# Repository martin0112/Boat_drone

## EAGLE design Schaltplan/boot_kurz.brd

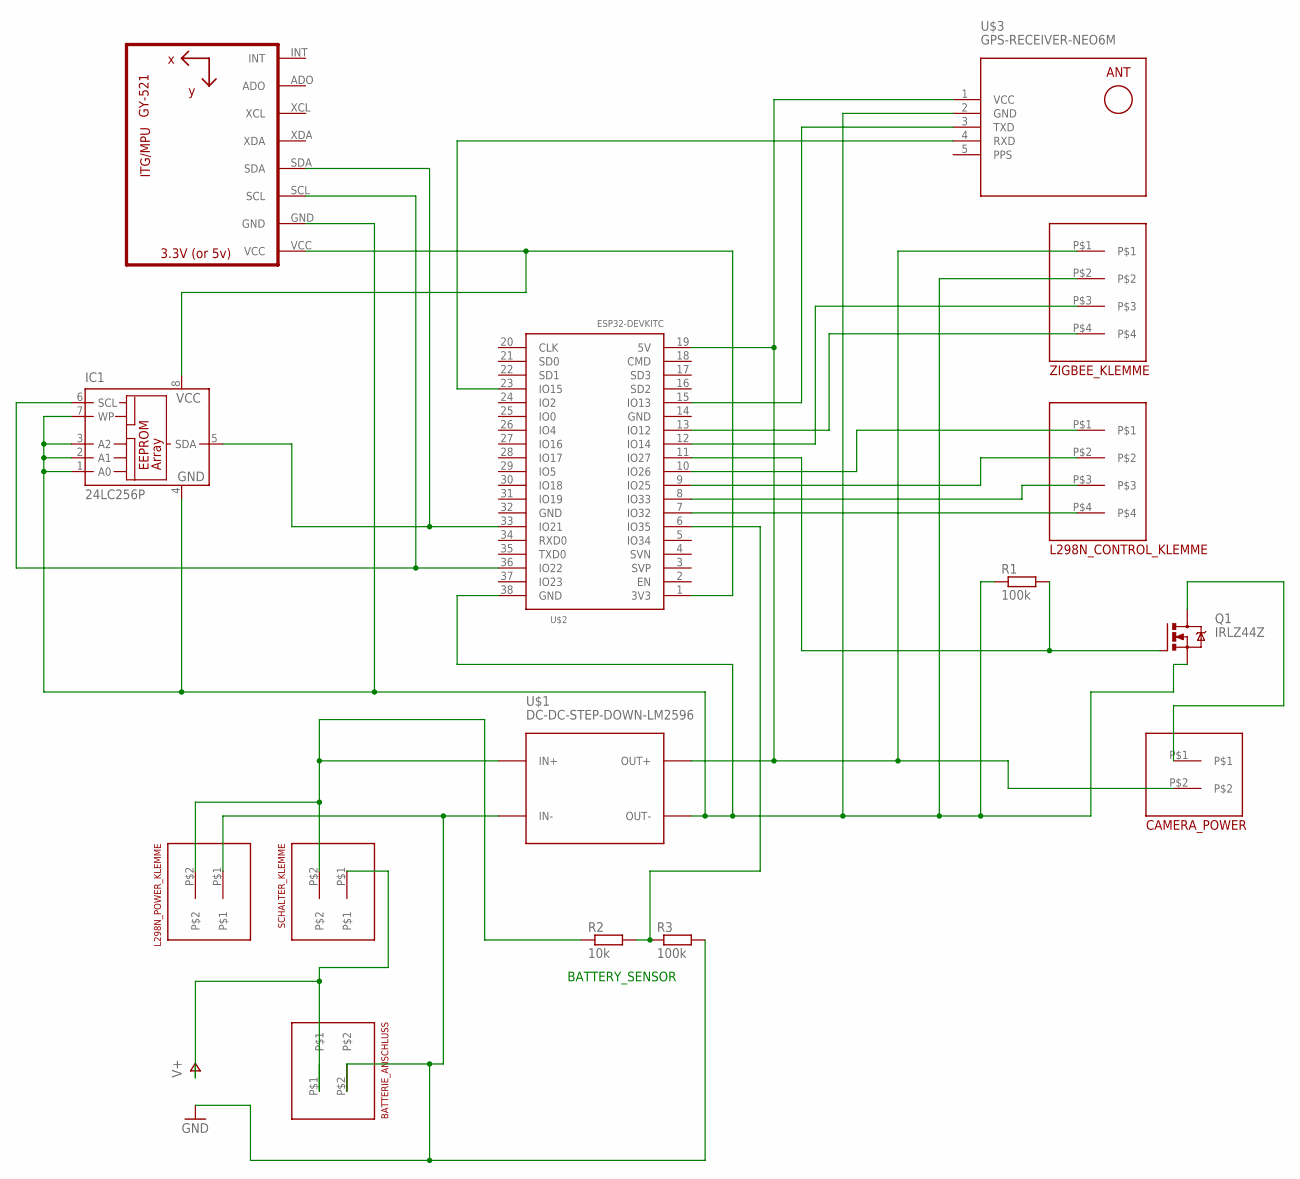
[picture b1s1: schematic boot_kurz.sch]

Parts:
BATTERIE_ANSCHLUSS: SCHRAUBKLEMME_X_2RM5.08; 2_PIN_RM5.08
CAMERA_POWER: AKL_349_X2; 2_PIN_AKL_349_BUCHSE
IC1: 24LC256P; DIL8
L298N_CONTROL_KLEMME: SCHRAUBKLEMME_X_4; 4_PIN_RM5.08_SCHRAUBKLEMME
L298N_POWER_KLEMME: SCHRAUBKLEMME_X_2RM5.08; 2_PIN_RM5.08
Q1: IRLZ44Z; TO220BH
R1, R3: 100k; 0207/7
R2: 10k; 0207/7
SCHALTER_KLEMME: SCHRAUBKLEMME_X_2RM5.08; 2_PIN_RM5.08
U1: GY-521MPU6050; GY-521
U$1: DC-DC-STEP-DOWN-LM2596
U$2: ESP32DEVKITC; ESP32-DEVKITC
U$3: GPS-RECEIVER-NEO6M
ZIGBEE_KLEMME: SCHRAUBKLEMME_X_4; 4_PIN_RM5.08_SCHRAUBKLEMME

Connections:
3.3V: IC1.8 (VCC), U1.VCC, U$2.1 (3V3)
5V: CAMERA_POWER.P$2, U$1.OUT+, U$2.19 (5V), U$3.1 (VCC), ZIGBEE_KLEMME.P$1
DRAIN: CAMERA_POWER.P$1, Q1.D
GATE: Q1.G, R1.2, U$2.11 (IO27)
GND: BATTERIE_ANSCHLUSS.P$2, L298N_POWER_KLEMME.P$1, R3.2, U$1.IN-
GROUND: IC1.1 (A0), IC1.2 (A1), IC1.3 (A2), IC1.4 (GND), IC1.7 (WP), Q1.S, R1.1, U1.GND, U$1.OUT-, U$2.38 (GND), U$3.2 (GND), ZIGBEE_KLEMME.P$2
unnamed: L298N_CONTROL_KLEMME.P$2, U$2.9 (IO25)
unnamed: L298N_CONTROL_KLEMME.P$3, U$2.8 (IO33)
unnamed: L298N_CONTROL_KLEMME.P$4, U$2.7 (IO32)
unnamed: L298N_CONTROL_KLEMME.P$1, U$2.10 (IO26)
unnamed: R2.2, R3.1, U$2.6 (IO35)
PPS: U$3.5 (PPS)
RX1: U$2.15 (IO13), U$3.3 (TXD)
RX2: U$2.12 (IO14), ZIGBEE_KLEMME.P$3
SCL: IC1.6 (SCL), U1.SCL, U$2.36 (IO22)
SDA: IC1.5 (SDA), U1.SDA, U$2.33 (IO21)
TX1: U$2.23 (IO15), U$3.4 (RXD)
TX2: U$2.13 (IO12), ZIGBEE_KLEMME.P$4
V+: BATTERIE_ANSCHLUSS.P$1, SCHALTER_KLEMME.P$1
V+_AFTER_SWITCH: L298N_POWER_KLEMME.P$2, R2.1, SCHALTER_KLEMME.P$2, U$1.IN+

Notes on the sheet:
BATTERY_SENSOR

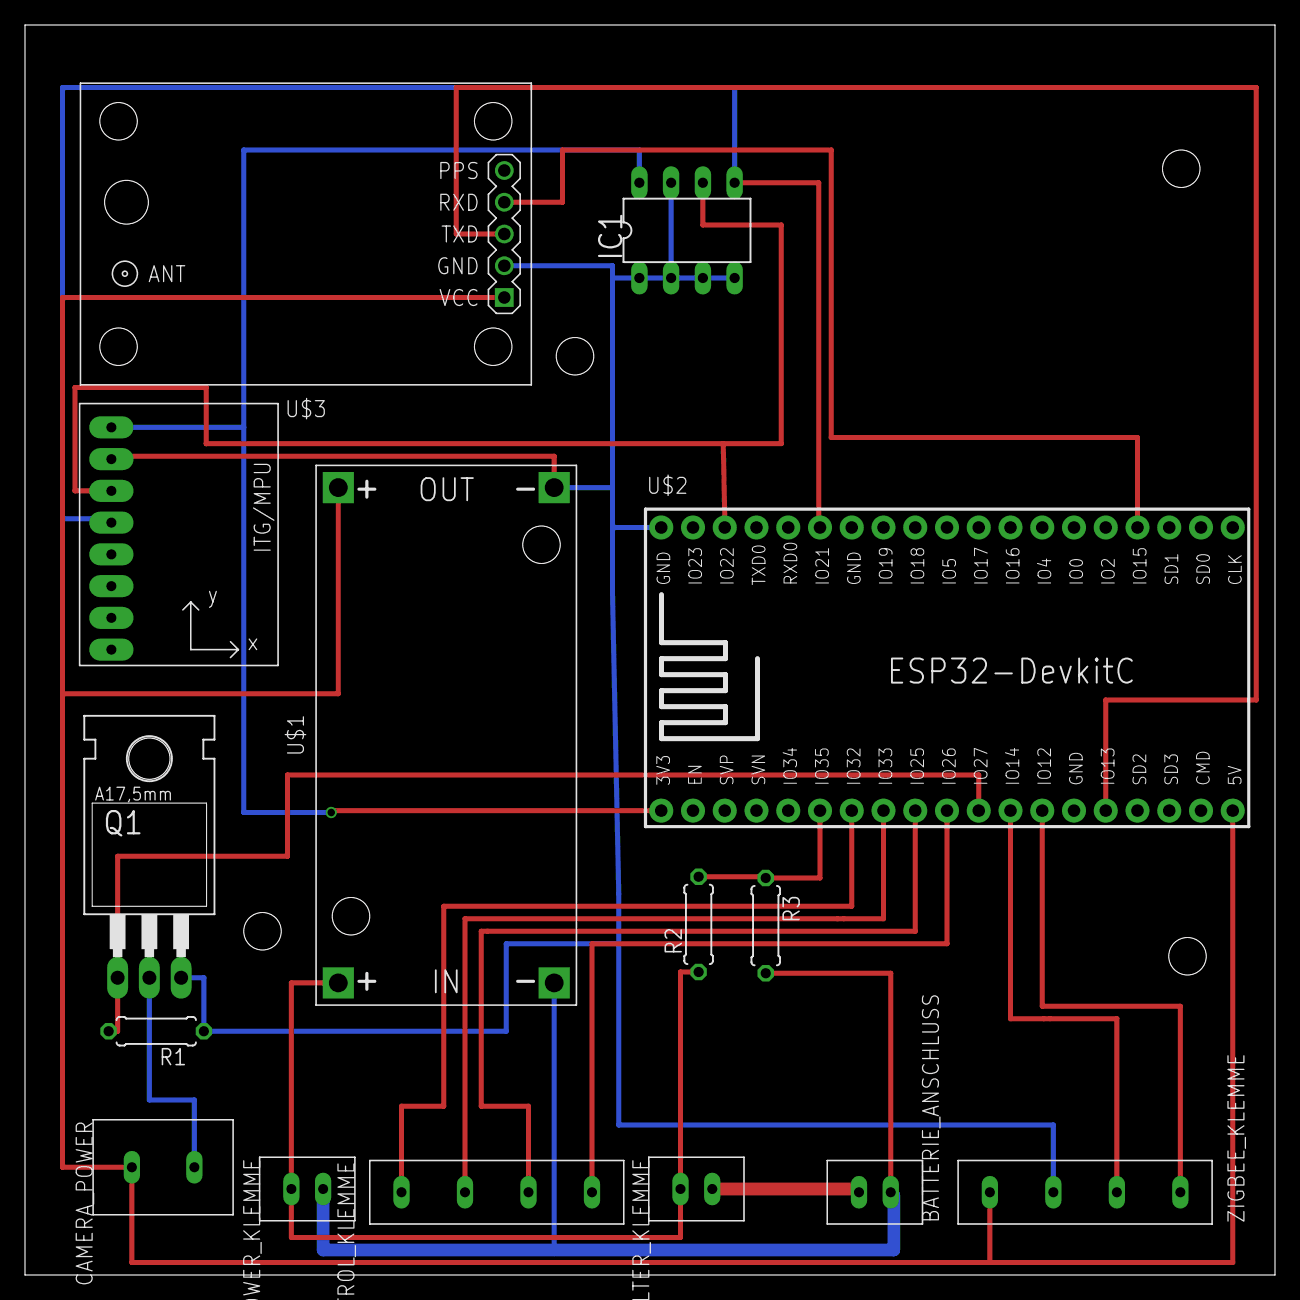
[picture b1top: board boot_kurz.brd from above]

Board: 2 copper layers, 100.0 x 100.0 mm, 15 parts (0 on the bottom side), 19 nets.

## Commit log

2020-05-23 1st hochladen
2022-06-22 Bump Newtonsoft.Json from 11.0.2 to 13.0.1 in /alt/hmi/HMI_II/Boat_New
    Bumps [Newtonsoft.Json](https://github.com/JamesNK/Newtonsoft.Json) from 11.0.2 to 13.0.1.
    - [Release notes](https://github.com/JamesNK/Newtonsoft.Json/releases)
    - [Commits](https://github.com/JamesNK/Newtonsoft.Json/compare/11.0.2...13.0.1)
    ---
    updated-dependencies:
    - dependency-name: Newtonsoft.Json
2022-06-22 Bump Newtonsoft.Json in /alt/Aervo_2_axis_hmi/Aervo_2_axis_hmi
    Bumps [Newtonsoft.Json](https://github.com/JamesNK/Newtonsoft.Json) from 9.0.1 to 13.0.1.
    - [Release notes](https://github.com/JamesNK/Newtonsoft.Json/releases)
    - [Commits](https://github.com/JamesNK/Newtonsoft.Json/compare/9.0.1...13.0.1)
    ---
    updated-dependencies:
    - dependency-name: Newtonsoft.Json
2022-06-22 Bump Newtonsoft.Json from 12.0.3 to 13.0.1 in /remote_II/remote_II
    Bumps [Newtonsoft.Json](https://github.com/JamesNK/Newtonsoft.Json) from 12.0.3 to 13.0.1.
    - [Release notes](https://github.com/JamesNK/Newtonsoft.Json/releases)
    - [Commits](https://github.com/JamesNK/Newtonsoft.Json/compare/12.0.3...13.0.1)
    ---
    updated-dependencies:
    - dependency-name: Newtonsoft.Json
2022-12-08 Bump Newtonsoft.Json from 11.0.2 to 13.0.2 in /alt/hmi/HMI_II/Boat_New
    Bumps [Newtonsoft.Json](https://github.com/JamesNK/Newtonsoft.Json) from 11.0.2 to 13.0.2.
    - [Release notes](https://github.com/JamesNK/Newtonsoft.Json/releases)
    - [Commits](https://github.com/JamesNK/Newtonsoft.Json/compare/11.0.2...13.0.2)
    ---
    updated-dependencies:
    - dependency-name: Newtonsoft.Json
2022-12-08 Bump Newtonsoft.Json from 12.0.3 to 13.0.2 in /remote_II/remote_II
    Bumps [Newtonsoft.Json](https://github.com/JamesNK/Newtonsoft.Json) from 12.0.3 to 13.0.2.
    - [Release notes](https://github.com/JamesNK/Newtonsoft.Json/releases)
    - [Commits](https://github.com/JamesNK/Newtonsoft.Json/compare/12.0.3...13.0.2)
    ---
    updated-dependencies:
    - dependency-name: Newtonsoft.Json

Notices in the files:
parts and their libraries:
lm2596_breakout: Released under the Creative Commons Attribution 4.0 International License: http://creativecommons.org/licenses/by/4.0
